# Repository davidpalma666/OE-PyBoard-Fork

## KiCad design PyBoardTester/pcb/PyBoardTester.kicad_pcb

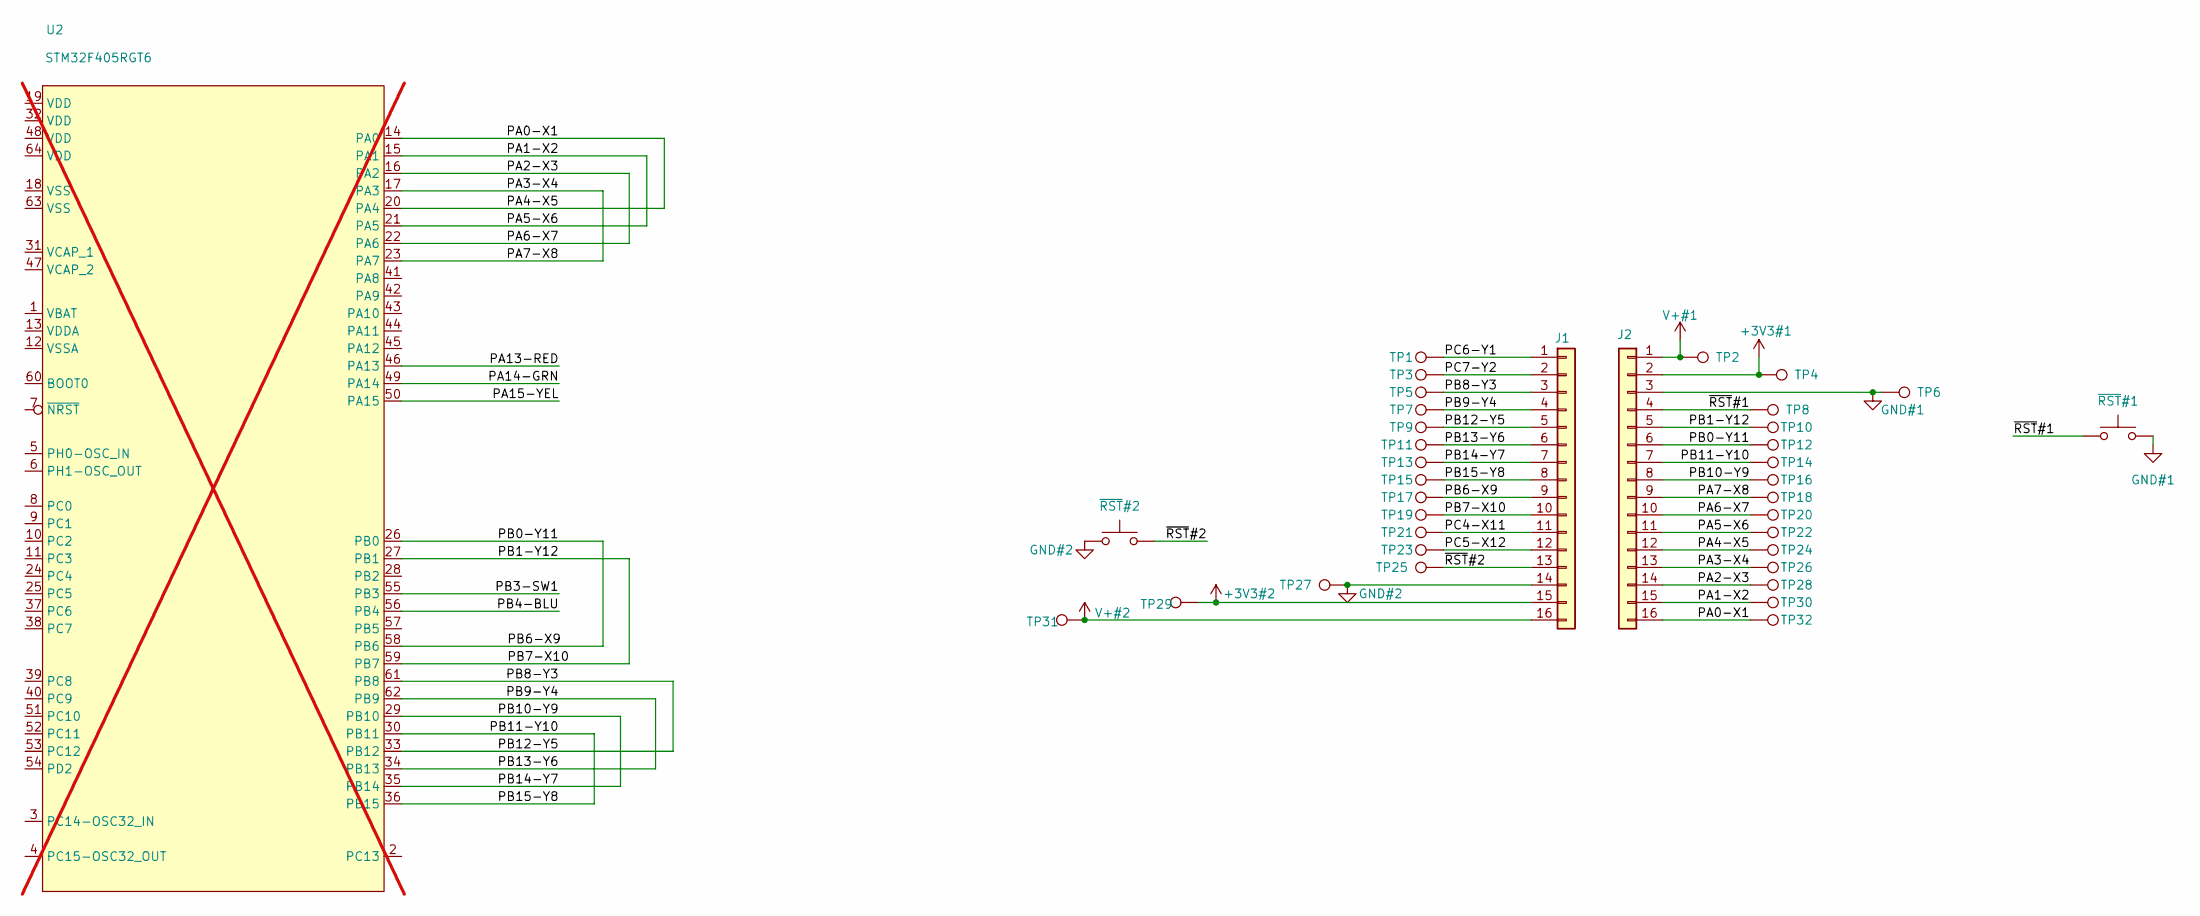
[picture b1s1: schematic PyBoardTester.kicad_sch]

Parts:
J1, J2: Conn_01x08; PinHeader_1x16_P2.54mm_Vertical; MPN TSW-116-06-T-S
TP1, TP2, TP3, TP4, TP5, TP7, TP8, TP9, TP10, TP11, TP12, TP13, TP14, TP15, TP16, TP17, TP18, TP19, TP20, TP21, TP22, TP23, TP24, TP25, TP26, TP28, TP29, TP30, TP31, TP32: TestPoint; TestPoint_Keystone_5015_Micro_Mini
TP6, TP27: TestPoint; TestPoint_Keystone_5000-5004_Miniature
U2: STM32F405RGT6; LQFP-64_10x10mm_P0.5mm; MPN STM32F405RGT6; not fitted
~{RST}#1, ~{RST}#2: SW_SPST; SWITCH TACTILE SPST-NO 0.05A 12V; MPN TL3305BF260QG

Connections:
+3V3#1: J2.2, TP4.1
+3V3#2: J1.15, TP29.1
/PA0-X1: J2.12, J2.16, TP24.1, TP32.1, U2.14 (PA0), U2.20 (PA4)
/PA1-X2: J2.11, J2.15, TP22.1, TP30.1, U2.15 (PA1), U2.21 (PA5)
/PA2-X3: J2.10, J2.14, TP20.1, TP28.1, U2.16 (PA2), U2.22 (PA6)
/PA3-X4: J2.9, J2.13, TP18.1, TP26.1, U2.17 (PA3), U2.23 (PA7)
/PB0-Y11: J1.9, J2.6, TP12.1, TP17.1, U2.26 (PB0), U2.58 (PB6)
/PB1-Y12: J1.10, J2.5, TP10.1, TP19.1, U2.27 (PB1), U2.59 (PB7)
/PB10-Y9: J1.7, J2.8, TP13.1, TP16.1, U2.29 (PB10), U2.35 (PB14)
/PB11-Y10: J1.8, J2.7, TP14.1, TP15.1, U2.30 (PB11), U2.36 (PB15)
/PB12-Y5: J1.3, J1.5, TP5.1, TP9.1, U2.33 (PB12), U2.61 (PB8)
/PB13-Y6: J1.4, J1.6, TP7.1, TP11.1, U2.34 (PB13), U2.62 (PB9)
/PC4-X11: J1.11, TP21.1
/PC5-X12: J1.12, TP23.1
/PC6-Y1: J1.1, TP1.1
/PC7-Y2: J1.2, TP3.1
/~RST#1: J2.4, TP8.1, ~{RST}#1.1
/~RST#2: J1.13, TP25.1, ~{RST}#2.2
GND#1: J2.3, TP6.1, ~{RST}#1.2
GND#2: J1.14, TP27.1, ~{RST}#2.1
V+#1: J2.1, TP2.1
V+#2: J1.16, TP31.1

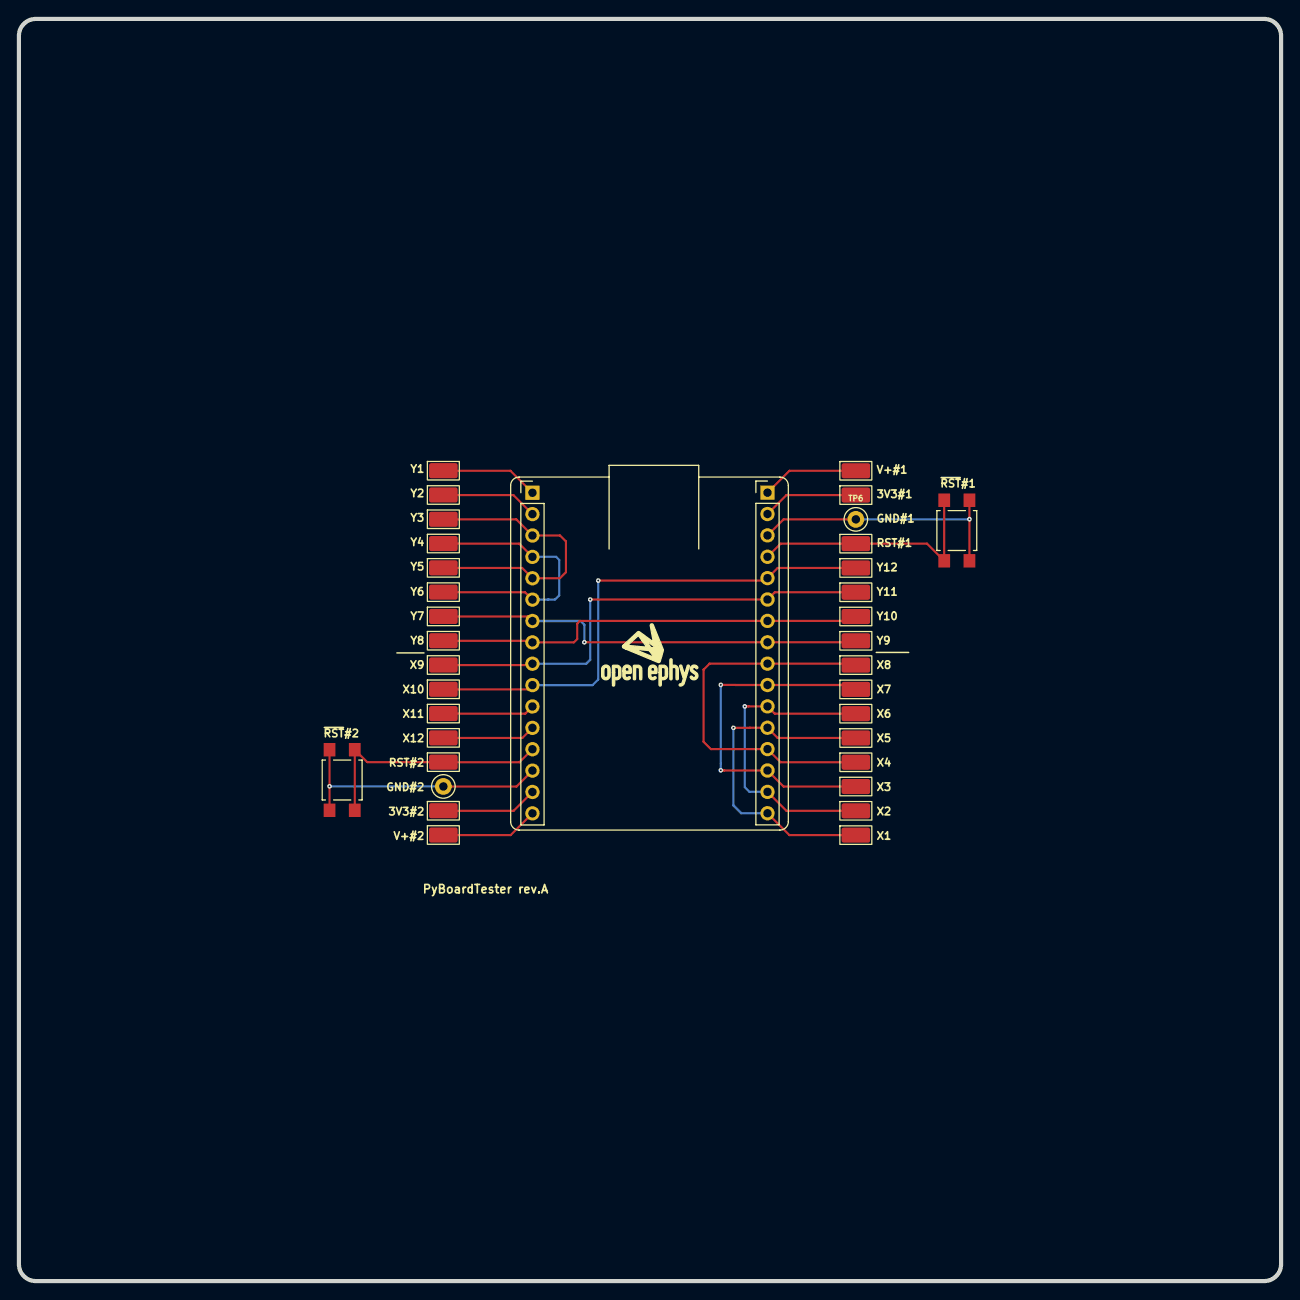
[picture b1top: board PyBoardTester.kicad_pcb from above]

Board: 2 copper layers, 150.0 x 150.0 mm, 34 parts (0 on the bottom side), 22 nets.

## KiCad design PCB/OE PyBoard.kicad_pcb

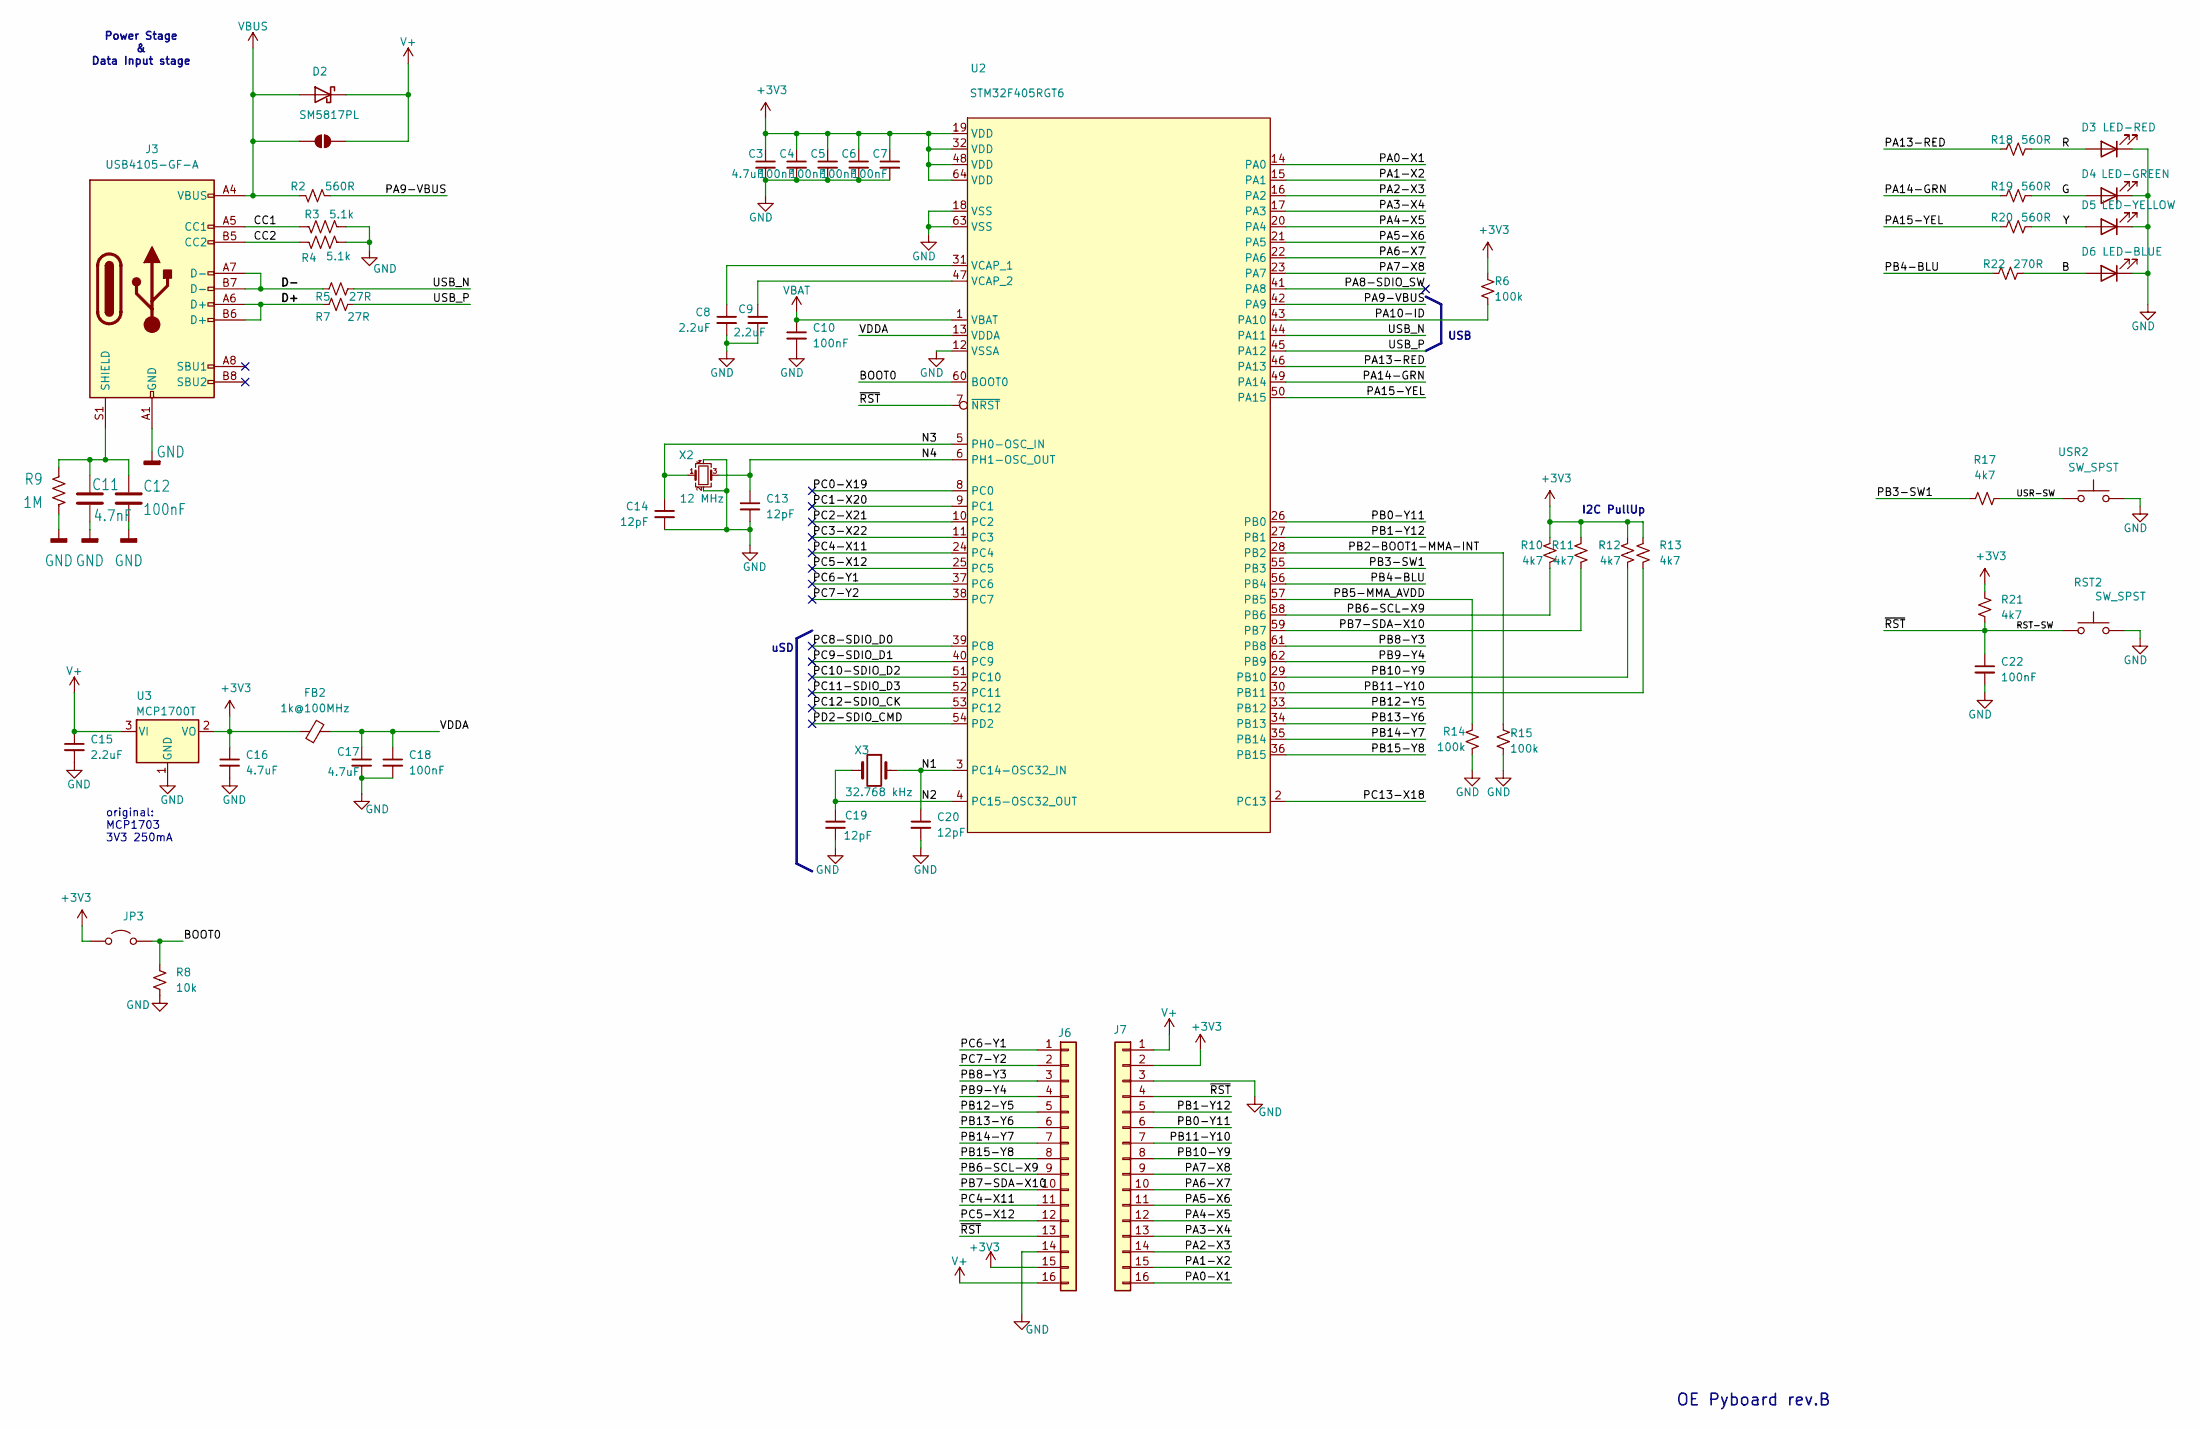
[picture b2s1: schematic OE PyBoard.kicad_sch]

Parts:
C3, C16, C17: 4.7uF; C_0603_1608Metric; MPN C1608X6S1C475K080AC
C4, C5, C6, C7, C10, C12, C18, C22: 100nF; C_0402_1005Metric; MPN CGA2B3X7R1H104K050BB
C8, C9, C15: 2.2uF; C_0603_1608Metric; MPN GRM188R61E225KA12D
C11: 4.7nF; C_0402_1005Metric; MPN 885012205084
C13, C14, C19, C20: 12pF; C_0402_1005Metric; MPN GRM1555C1H120JA01D
D2: SM5817PL; D_SOD-123; MPN SM5817PL-TP
D3: LED-RED; LED_0603_1608Metric; MPN 5975004407F
D4: LED-GREEN; LED_0603_1608Metric; MPN LSM0603453V
D5: LED-YELLOW; LED_0603_1608Metric; MPN 5990040007F
D6: LED-BLUE; LED_0603_1608Metric; MPN 5988D90107F
FB2: 1k@100MHz; L_0402_1005Metric; MPN BLM15HD102SN1D
J3: USB4105-GF-A; USB_C_Receptacle_GCT_USB4105-xx-A_16P_TopMnt_Horizontal; MPN USB4105-GF-A
J6, J7: Conn_01x08; PinHeader_1x16_P2.54mm_Vertical; MPN CES-116-01-T-S
JP2: 0R; SolderJumper-2_P1.3mm_Open_RoundedPad1.0x1.5mm
JP3: Jumper; PinHeader_1x02_P2.54mm_Vertical
R2, R18, R19, R20: 560R; R_0402_1005Metric; MPN CRCW0402560RFKED
R3, R4: 5.1k; R_0402_1005Metric; MPN ERJ-2RKF5101X
R5, R7: 27R; R_0402_1005Metric; MPN RMCF0402FT27R0
R6, R14, R15: 100k; R_0402_1005Metric; MPN AC0402FR-07100KL
R8: 10k; R_0402_1005Metric; MPN ERJ-2RKF1002X
R9: 1M; R_0402_1005Metric; MPN CRCW04021M00FKED
R10, R11, R12, R13, R17, R21: 4k7; R_0402_1005Metric; MPN ERJ-2RKF4701X
R22: 270R; R_0402_1005Metric; MPN CRCW0402270RFKEDC
RST2: SW_SPST; SW_SPST_TL3305B; MPN TL3305BF260QG
U2: STM32F405RGT6; LQFP-64_10x10mm_P0.5mm; MPN STM32F405RGT6
U3: MCP1700T; SOT-23; MPN MCP1700T-3302E/TT
USR2: SW_SPST; SW_SPST_TL3305B; MPN TL3305BF260QG
X2: 12 MHz; Crystal_SMD_Abracon_ABM8AIG-4Pin_3.2x2.5mm; MPN ABM8AIG-12.000MHZ-12-2Z-T3
X3: 32.768 kHz; Crystal_SMD_2012-2Pin_2.0x1.2mm_HandSoldering; MPN 9HT11-32.768KBZF-T

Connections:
+3V3: C3.1, C4.1, C5.1, C6.1, C7.1, C16.1, FB2.1, J6.15, J7.2, JP3.2 (B), R6.1, R10.1, R11.1, R12.1, R13.1, R21.2, U2.19 (VDD), U2.32 (VDD), U2.48 (VDD), U2.64 (VDD), U3.2 (VO)
/B: D6.2 (A), R22.2
/BOOT0: JP3.1 (A), R8.1, U2.60 (BOOT0)
/CC1: J3.A5 (CC1), R3.1
/CC2: J3.B5 (CC2), R4.1
/D+: J3.A6 (D+), J3.B6 (D+), R7.2
/D-: J3.A7 (D-), J3.B7 (D-), R5.2
/G: D4.2 (A), R19.2
/N3: C14.1, U2.5 (PH0-OSC_IN), X2.1
/N4: C13.1, U2.6 (PH1-OSC_OUT), X2.3
/PA0-X1: J7.16, U2.14 (PA0)
/PA1-X2: J7.15, U2.15 (PA1)
/PA2-X3: J7.14, U2.16 (PA2)
/PA3-X4: J7.13, U2.17 (PA3)
/PA4-X5: J7.12, U2.20 (PA4)
/PA5-X6: J7.11, U2.21 (PA5)
/PA6-X7: J7.10, U2.22 (PA6)
/PA7-X8: J7.9, U2.23 (PA7)
/PA8-SDIO_SW: U2.41 (PA8)
/PA9-VBUS: R2.1, U2.42 (PA9)
/PA10-ID: R6.2, U2.43 (PA10)
/PA13-RED: R18.1, U2.46 (PA13)
/PA14-GRN: R19.1, U2.49 (PA14)
/PA15-YEL: R20.1, U2.50 (PA15)
/PB0-Y11: J7.6, U2.26 (PB0)
/PB1-Y12: J7.5, U2.27 (PB1)
/PB2-BOOT1-MMA-INT: R15.1, U2.28 (PB2)
/PB3-SW1: R17.1, U2.55 (PB3)
/PB4-BLU: R22.1, U2.56 (PB4)
/PB5-MMA_AVDD: R14.1, U2.57 (PB5)
/PB6-SCL-X9: J6.9, R10.2, U2.58 (PB6)
/PB7-SDA-X10: J6.10, R11.2, U2.59 (PB7)
/PB8-Y3: J6.3, U2.61 (PB8)
/PB9-Y4: J6.4, U2.62 (PB9)
/PB10-Y9: J7.8, R12.2, U2.29 (PB10)
/PB11-Y10: J7.7, R13.2, U2.30 (PB11)
/PB12-Y5: J6.5, U2.33 (PB12)
/PB13-Y6: J6.6, U2.34 (PB13)
/PB14-Y7: J6.7, U2.35 (PB14)
/PB15-Y8: J6.8, U2.36 (PB15)
/PC0-X19: U2.8 (PC0)
/PC1-X20: U2.9 (PC1)
/PC2-X21: U2.10 (PC2)
/PC3-X22: U2.11 (PC3)
/PC4-X11: J6.11, U2.24 (PC4)
/PC5-X12: J6.12, U2.25 (PC5)
/PC6-Y1: J6.1, U2.37 (PC6)
/PC7-Y2: J6.2, U2.38 (PC7)
/PC8-SDIO_D0: U2.39 (PC8)
/PC9-SDIO_D1: U2.40 (PC9)
/PC10-SDIO_D2: U2.51 (PC10)
/PC11-SDIO_D3: U2.52 (PC11)
/PC12-SDIO_CK: U2.53 (PC12)
/PC13-X18: U2.2 (PC13)
/PD2-SDIO_CMD: U2.54 (PD2)
/R: D3.2 (A), R18.2
/RST-SW: C22.1, J6.13, J7.4, R21.1, RST2.1, U2.7 (~NRST)
/USB_N: R5.1, U2.44 (PA11)
/USB_P: R7.1, U2.45 (PA12)
/USR-SW: R17.2, USR2.1
/VDDA: C17.1, C18.1, FB2.2, U2.13 (VDDA)
/Y: D5.2 (A), R20.2
GND: C3.2, C4.2, C5.2, C6.2, C7.2, C8.2, C9.2, C10.2, C11.2, C12.1, C13.2, C14.2, C15.2, C16.2, C17.2, C18.2, C19.2, C20.2, C22.2, D3.1 (K), D4.1 (K), D5.1 (K), D6.1 (K), J3.A1 (GND), J3.A12 (GND), J3.B1 (GND), J3.B12 (GND), J6.14, J7.3, R3.2, R4.2, R8.2, R9.1, R14.2, R15.2, RST2.2, U2.12 (VSSA), U2.18 (VSS), U2.63 (VSS), U3.1 (GND), USR2.2, X2.2, X2.4
unnamed: C11.1, C12.2, J3.S1 (SHIELD), R9.2
unnamed: C8.1, U2.31 (VCAP_1)
unnamed: C9.1, U2.47 (VCAP_2)
V+: C15.1, D2.1 (K), J6.16, J7.1, JP2.2 (B), U3.3 (VI)
VBAT: C10.1, U2.1 (VBAT)
VBUS: D2.2 (A), J3.A4 (VBUS), J3.A9 (VBUS), J3.B4 (VBUS), J3.B9 (VBUS), JP2.1 (A), R2.2

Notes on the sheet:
I2C PullUp
USB
original: MCP1703 3V3 250mA
uSD
OE Pyboard rev.B
Power Stage & Data Input stage

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
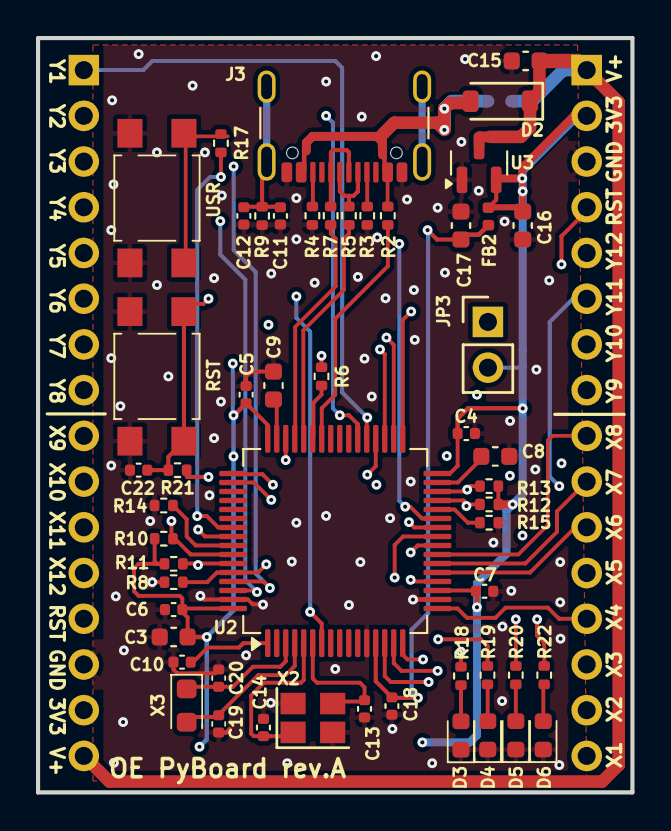
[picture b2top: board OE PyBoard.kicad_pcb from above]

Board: 4 copper layers, 33.0 x 41.9 mm, 56 parts (1 on the bottom side), 59 nets.

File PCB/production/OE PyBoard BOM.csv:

#;Qty;Reference;Value;DNP;OEPSPN;MPN;Footprint
1;4;C13,C14,C19,C20;12pF;;OEPS010086;GRM1555C1H120JA01D;Capacitor_SMD:C_0402_1005Metric
2;1;C11;4.7nF;;OEPS010017;885012205084;Capacitor_SMD:C_0402_1005Metric
3;8;C4,C5,C6,C7,C10,C12,C18,C22;100nF;;OEPS010016;CGA2B3X7R1H104K050BB;Capacitor_SMD:C_0402_1005Metric
4;3;C8,C9,C15;2.2uF;;OEPS010075;GRM188R61E225KA12D;Capacitor_SMD:C_0603_1608Metric
5;3;C3,C16,C17;4.7uF;;OEPS010018;C1608X6S1C475K080AC;Capacitor_SMD:C_0603_1608Metric
6;1;X2;12 MHz;;OEPS100059;ABM8AIG-12.000MHZ-12-2Z-T3;Crystal:Crystal_SMD_Abracon_ABM8AIG-4Pin_3.2x2.5mm
7;2;R5,R7;27R;;OEPS020170;RMCF0402FT27R0;Resistor_SMD:R_0402_1005Metric
8;1;X3;32.768 kHz;;OEPS100051;9HT11-32.768KBZF-T;Crystal:Crystal_SMD_2012-2Pin_2.0x1.2mm_HandSoldering
9;1;R22;270R;;OEPS020060;CRCW0402270RFKEDC;Resistor_SMD:R_0402_1005Metric
10;4;R2,R18,R19,R20;560R;;OEPS020193;CRCW0402560RFKED;Resistor_SMD:R_0402_1005Metric
11;2;R3,R4;5.1k;;OEPS020173;ERJ-2RKF5101X;Resistor_SMD:R_0402_1005Metric
12;1;R8;10k;;OEPS020013;ERJ-2RKF1002X;Resistor_SMD:R_0402_1005Metric
13;3;R6,R14,R15;100k;;OEPS020051;AC0402FR-07100KL;Resistor_SMD:R_0402_1005Metric
14;1;R9;1M;;OEPS020026;CRCW04021M00FKED;Resistor_SMD:R_0402_1005Metric
15;1;FB2;1k@100MHz;;OEPS040013;BLM15HD102SN1D;Inductor_SMD:L_0402_1005Metric
16;6;R10,R11,R12,R13,R17,R21;4k7;;OEPS020010;ERJ-2RKF4701X;Resistor_SMD:R_0402_1005Metric
17;2;J6,J7;Conn_01x08;;OEPS070110;CES-116-01-T-S;Connector_PinHeader_2.54mm:PinHeader_1x16_P2.54mm_Vertical
18;1;JP3;Jumper;;;;Connector_PinHeader_2.54mm:PinHeader_1x02_P2.54mm_Vertical
19;1;D6;LED-BLUE;;OEPS030042;5988D90107F;LED_SMD:LED_0603_1608Metric
20;1;D4;LED-GREEN;;OEPS030032;LSM0603453V;LED_SMD:LED_0603_1608Metric
21;1;D3;LED-RED;;OEPS030006;5975004407F;LED_SMD:LED_0603_1608Metric
22;1;D5;LED-YELLOW;;OEPS030043;5990040007F;LED_SMD:LED_0603_1608Metric
23;1;U3;MCP1700T;;OEPS080153;MCP1700T-3302E/TT;Package_TO_SOT_SMD:SOT-23
24;1;D2;SM5817PL;;OEPS030030;SM5817PL-TP;Diode_SMD:D_SOD-123
25;1;U2;STM32F405RGT6;;OEPS080178;STM32F405RGT6;Package_QFP:LQFP-64_10x10mm_P0.5mm
26;2;RST2,USR2;SW_SPST;;OEPS100061;TL3305BF260QG;Button_Switch_SMD:SW_SPST_TL3305B
27;1;J3;USB4105-GF-A;;OEPS070105;USB4105-GF-A;Connector_USB:USB_C_Receptacle_GCT_USB4105-xx-A_16P_TopMnt_Horizontal

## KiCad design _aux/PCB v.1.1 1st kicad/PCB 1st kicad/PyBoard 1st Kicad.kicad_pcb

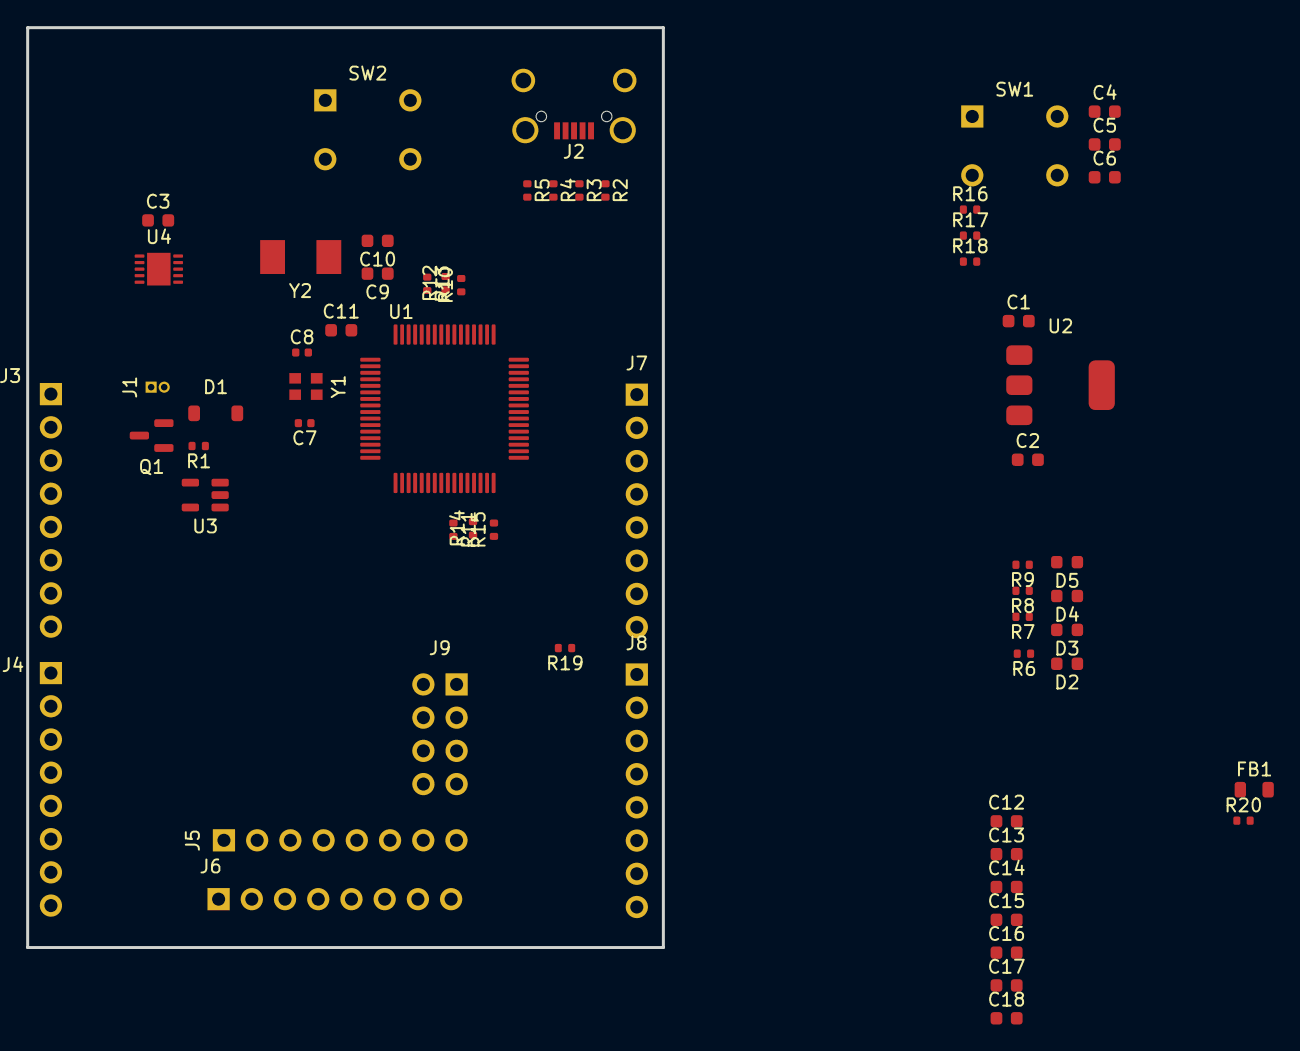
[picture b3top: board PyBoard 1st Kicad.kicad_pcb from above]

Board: 2 copper layers, 48.6 x 70.3 mm, 62 parts (0 on the bottom side), 65 nets, no tracks yet.

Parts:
C1, C3, C4, C5: 2u2; C_0603_1608Metric
C2: 4u7; C_0603_1608Metric
C6, C11, C12, C13, C14, C15, C18: 100n; C_0603_1608Metric
C7, C8: 10p; C_0402_1005Metric
C9, C10: 2p2; C_0603_1608Metric
C16, C17: 4.7u; C_0603_1608Metric
D1: MSE1PB-M3/89A; D_SOD-123
D2: LED-RED; LED_0603_1608Metric
D3: LED-GREEN; LED_0603_1608Metric
D4: LED-YELLOW; LED_0603_1608Metric
D5: LED-BLUE; LED_0603_1608Metric
FB1: 1k; L_0805_2012Metric
J1: Conn_01x02; PinHeader_1x02_P1.00mm_Vertical
J2: USB_B_Micro; USB_Micro-B_Wuerth_629105150521_CircularHoles
J3, J4, J5, J6, J7, J8: Conn_01x08; PinHeader_1x08_P2.54mm_Vertical
J9: Conn_02x04_Odd_Even; PinSocket_2x04_P2.54mm_Vertical
Q1: DMP2160UW; SOT-23
R1, R10, R11, R17, R19: 100k; R_0402_1005Metric
R2, R5, R6, R7, R8: 560R; R_0402_1005Metric
R3, R4: 22R; R_0402_1005Metric
R9, R20: 220R; R_0402_1005Metric
R12, R13, R14, R15, R16, R18: 4k7; R_0402_1005Metric
SW1, SW2: SW_MEC_5E; SW_TH_Tactile_Omron_B3F-10xx
U1: STM32F405RGT6; LQFP-64_10x10mm_P0.5mm
U2: MCP1703 3V3; SOT-223-3_TabPin2
U3: MIC2005A-1YM5; SOT-23-5
U4: MMA7660; WDFN-10-1EP_3x3mm_P0.5mm_EP1.8x2.5mm
Y1: Crystal_GND24; Crystal_SMD_Abracon_ABM10-4Pin_2.5x2.0mm
Y2: Crystal; Crystal_SMD_Abracon_ABM7-2Pin_6.0x3.5mm

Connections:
+3V3: C2.1, C12.1, C13.1, C14.1, C15.1, C16.1, FB1.1, J4.7, J7.2, R12.1, R13.1, R14.1, R15.1, R18.1, R19.1, U1.19 (VDD), U1.32 (VDD), U1.48 (VDD), U1.64 (VDD), U2.3 (VO), U4.9 (DVDD)
+5V: C1.1, D1.1 (K), J4.8, J5.7, J7.1, Q1.2 (S), U2.1 (VI), U3.1 (VIN)
/B: D5.2 (A), R9.2, U3.3 (EN)
/BOOT0-P1: J5.1, R17.1, U1.60 (BOOT0/VPP)
/D+: J2.3 (D+), R3.2
/D-: J2.2 (D-), R4.2
/G: D3.2 (A), R7.2
/ID: J2.4 (ID), R5.2
/N1: C9.1, U1.3 (PC14-OSC32_IN(PC14)/EVENTOUT/OSC32_IN), Y2.1
/N2: C10.1, U1.4 (PC15-OSC32_OUT(PC15)/EVENTOUT/OSC32_OUT), Y2.2
/N3: C8.1, U1.5 (PH0-OSC_IN(PH0)/EVENTOUT/OSC_IN), Y1.1
/N4: C7.1, U1.6 (PH1-OSC_OUT(PH1)/EVENTOUT/OSC_OUT), Y1.4
/PA0-X1: J8.8, U1.14 (PA0-WKUP(PA0)/USART2_CTS/UART4_TX/ETH_M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)
/PA1-X2: J8.7, U1.15 (PA1/USART2_RTS/UART4_RX/ETH_RMII_REF_CL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)
/PA2-X3: J8.6, U1.16 (PA2/USART2_TX/TIM5_CH3/TIM9_CH1/TIM2_CH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)
/PA3-X4: J8.5, U1.17 (PA3/USART2_RX/TIM5_CH4/TIM9_CH2/TIM2_CH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)
/PA4-X5: J8.4, U1.20 (PA4/SPI1_NSS/SPI3_NSS/USART2_CK/DCMI_HS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)
/PA5-X6: J8.3, U1.21 (PA5/SPI1_SCK/OTG_HS_ULPI_CK/TIM2_CH1_ET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)
/PA6-X7: J8.2, U1.22 (PA6/SPI1_MISO/TIM8_BKIN/TIM13_CH1/DCMI_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)
/PA7-X8: J8.1, U1.23 (PA7/SPI1_MOSI/TIM8_CH1N/TIM14_CH1/TIM3_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)
/PA9-VBUS: R2.1, U1.42 (PA9/USART1_TX/TIM1_CH2/I2C3_SMBA/DCMI_D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)
/PA10-ID: R5.1, R19.2, U1.43 (PA10/USART1_RX/TIM1_CH3/OTG_FS_ID/DCMI_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)
/PA11-DM: R4.1, U1.44 (PA11/USART1_CTS/CAN1_RX/TIM1_CH4/OTG_FS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)
/PA12-DP: R3.1, U1.45 (PA12/USART1_RTS/CAN1_TX/TIM1_ETR/OTG_FS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)
/PA13-RED-P5: J5.5, R6.1, U1.46 (PA13(JTMS-SWDIO)/JTMS-SWDIO/EVENTOUT)
/PA14-GRN-P4: J5.4, R7.1, U1.49 (PA14(JTCK-SWCLK)/JTCK-SWCLK/EVENTOUT)
/PA15-YEL-P3: J5.3, R8.1, U1.50 (PA15(JTDI)/JTDI/SPI3_NSS/I2S3_WS/TIM2_C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)
/PB0-Y11: J7.6, U1.26 (PB0/TIM3_CH3/TIM8_CH2N/OTG_HS_ULPI_D1/E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)
/PB1-Y12: J7.5, U1.27 (PB1/TIM3_CH4/TIM8_CH3N/OTG_HS_ULPI_D2/E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)
/PB2-BOOT1-MMA-INT: R11.1, U1.28 (PB2-BOOT1(PB2)/EVENTOUT), U4.5 (~INT)
/PB3-SW-X17: J6.1, R16.1, U1.55 (PB3(JTDO/TRACESWO)/JTDO/TRACESWO/SPI3_S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)
/PB4-BLU-P2: J5.2, R9.1, U1.56 (PB4(NJTRST)/NJTRST/SPI3_MISO/TIM3_CH1/S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)
/PB5-MMA_AVDD: C3.1, R10.1, U1.57 (PB5/I2C1_SMBA/CAN2_RX/OTG_HS_ULPI_D7/ET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), U4.3 (AVDD)
/PB6-SCL-X9: J4.1, R12.2, U1.58 (PB6/I2C1_SCL/TIM4_CH1/CAN2_TX/DCMI_D5/U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), U4.6 (SCL)
/PB7-SDA-X10: J4.2, R13.2, U1.59 (PB7/I2C1_SDA/FSMC_NL/DCMI_VSYNC/USART1_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), U4.7 (SDA)
/PB8-Y3: J3.3, U1.61 (PB8/TIM4_CH3/SDIO_D4/TIM10_CH1/DCMI_D6/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)
/PB9-Y4: J3.4, U1.62 (PB9/SPI2_NSS/I2S2_WS/TIM4_CH4/TIM11_CH1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)
/PB10-Y9: J7.8, R14.2, U1.29 (PB10/SPI2_SCK/I2S2_CK/I2C2_SCL/USART3_T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)
/PB11-Y10: J7.7, R15.2, U1.30 (PB11/I2C2_SDA/USART3_RX/OTG_HS_ULPI_D4/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)
/PB12-Y5: J3.5, U1.33 (PB12/SPI2_NSS/I2S2_WS/I2C2_SMBA/USART3_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)
/PB13-Y6: J3.6, U1.34 (PB13/SPI2_SCK/I2S2_CK/USART3_CTS/TIM1_C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)
/PB14-Y7: J3.7, U1.35 (PB14/SPI2_MISO/TIM1_CH2N/TIM12_CH1/OTG_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)
/PB15-Y8: J3.8, U1.36 (PB15/SPI2_MOSI/I2S2_SD/TIM1_CH3N/TIM8_C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)
/PC0-X19: J6.3, U1.8 (PC0/OTG_HS_ULPI_STP/EVENTOUT/ADC123_IN10)
/PC1-X20: J6.4, U1.9 (PC1/ETH_MDC/EVENTOUT/ADC123_IN11)
/PC2-X21: J6.5, U1.10 (PC2/SPI2_MISO/OTG_HS_ULPI_DIR/ETH_MII_T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)
/PC3-X22: J6.6, U1.11 (PC3/SPI2_MOSI/I2S2_SD/OTG_HS_ULPI_NXT/E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)
/PC4-X11: J4.3, U1.24 (PC4/ETH_RMII_RX_D0/ETH_MII_RX_D0/EVENTO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)
/PC5-X12: J4.4, U1.25 (PC5/ETH_RMII_RX_D1/ETH_MII_RX_D1/EVENTO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)
/PC6-Y1: J3.1, U1.37 (PC6/I2S2_MCK/TIM8_CH1/SDIO_D6/USART6_TX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)
/PC7-Y2: J3.2, U1.38 (PC7/I2S3_MCK/TIM8_CH2/SDIO_D7/USART6_RX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)
/PC13-X18: J6.2, U1.2 (PC13/EVENTOUT/RTC_OUT,RTC_TAMP1,RTC_TS)
/R: D2.2 (A), R6.2
/RST#: C6.1, J4.5, J7.4, R18.2, U1.7 (NRST)
/USR-SW: R16.2, SW2.1
/VBUS: D1.2 (A), J2.1 (VBUS), R1.2, R2.2, U3.5 (VOUT)
/VCAP1: C4.1, U1.31 (VCAP_1)
/VCAP2: C5.1, U1.47 (VCAP_2)
/Y: D4.2 (A), R8.2
A3V3: C17.1, C18.1, FB1.2, J6.7, U1.13 (VDDA)
GND: C1.2, C2.2, C3.2, C4.2, C5.2, C6.2, C7.2, C8.2, C9.2, C10.2, C11.2, C12.2, C13.2, C14.2, C15.2, C16.2, C17.2, C18.2, D2.1 (K), D3.1 (K), D4.1 (K), D5.1 (K), J1.2, J2.5 (GND), J2.6 (Shield), J4.6, J5.8, J6.8, J7.3, R10.2, R11.2, R17.2, SW1.2, U1.12 (VSSA), U1.18 (VSS), U1.63 (VSS), U2.2 (GND), U3.2 (GND), U4.1 (RSRVD), U4.2 (N.C.), U4.4 (AVSS), U4.8 (DVSS), U4.10 (RSRVD), Y1.2, Y1.3
unnamed: J5.6, R20.2
unnamed: Q1.1 (G), R1.1
VBACKUP: C11.1, R20.1, U1.1 (VBAT)
VBAT: J1.1, Q1.3 (D)

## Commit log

2025-10-01 rev B - inicio
2025-10-09 . preparada para produção
    - demoninação rev.B passada a rev.A
    - criados ficheiros de produção:
    . Gerbers & Drills
    . IPC-2581
    . OE PyBoard BOM
2025-12-09 re-tunning...
    - tunning from main branch to fork
    - fork already had files & folders that had to be deleted - conflict issues
    - files & folder structure now rebuilt as-it-was on 'my fork', before solving conflict issues:
    . new files about pyBoardTester PCBc
    . _aux folder
